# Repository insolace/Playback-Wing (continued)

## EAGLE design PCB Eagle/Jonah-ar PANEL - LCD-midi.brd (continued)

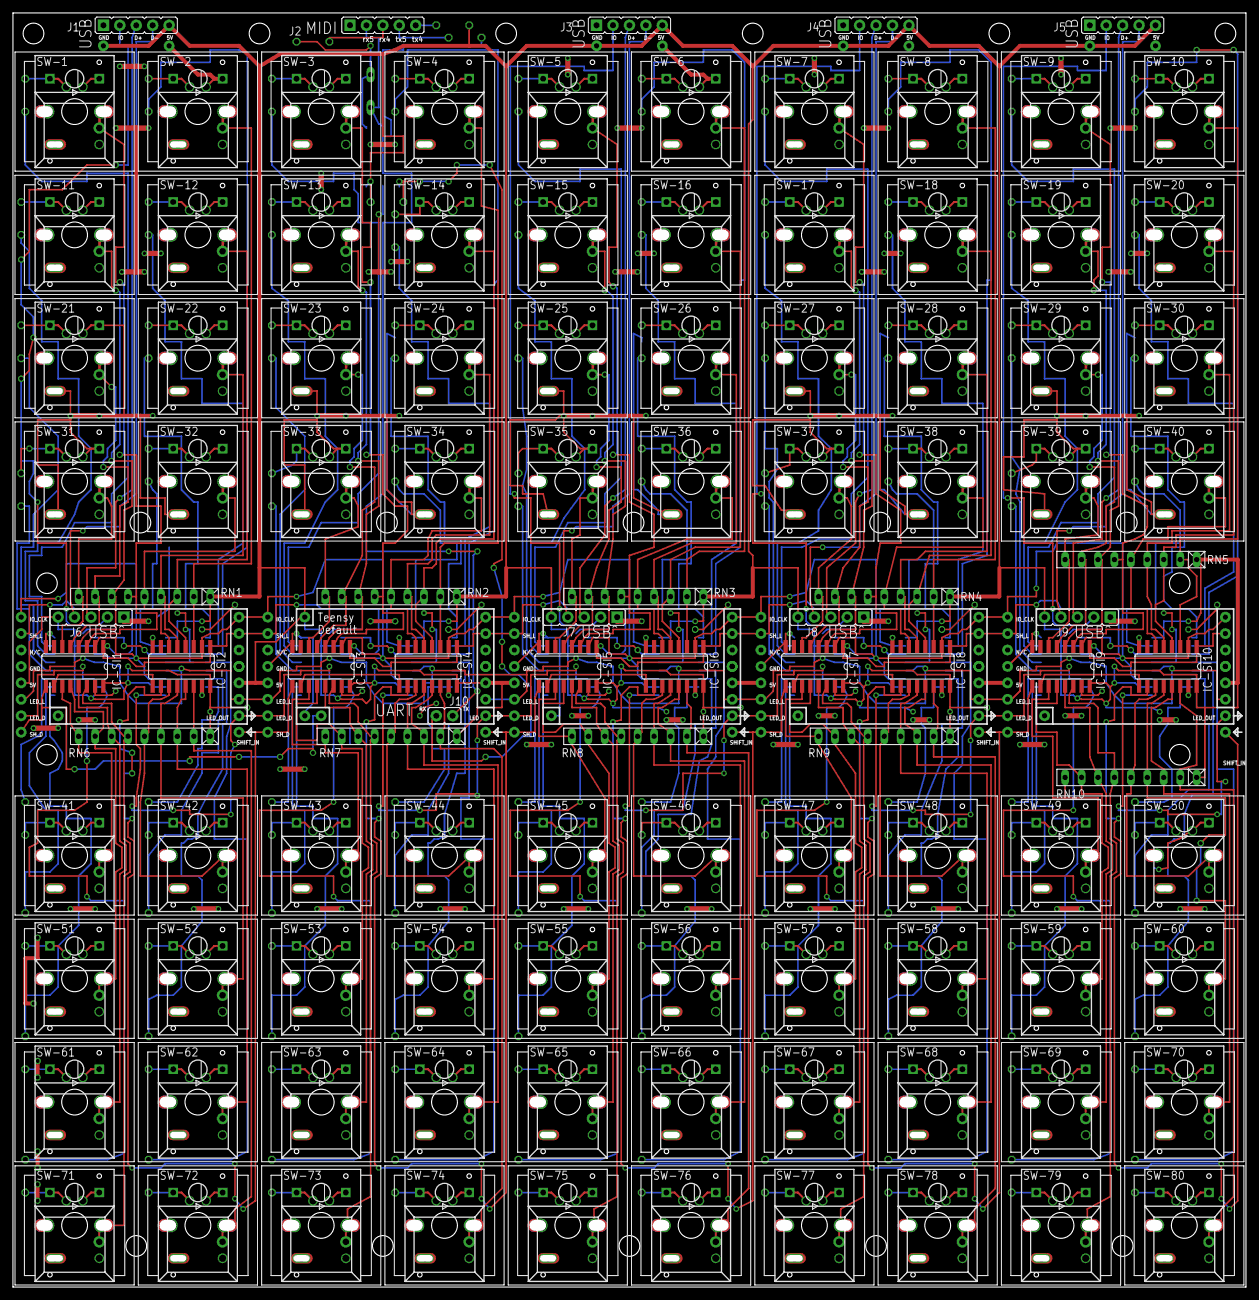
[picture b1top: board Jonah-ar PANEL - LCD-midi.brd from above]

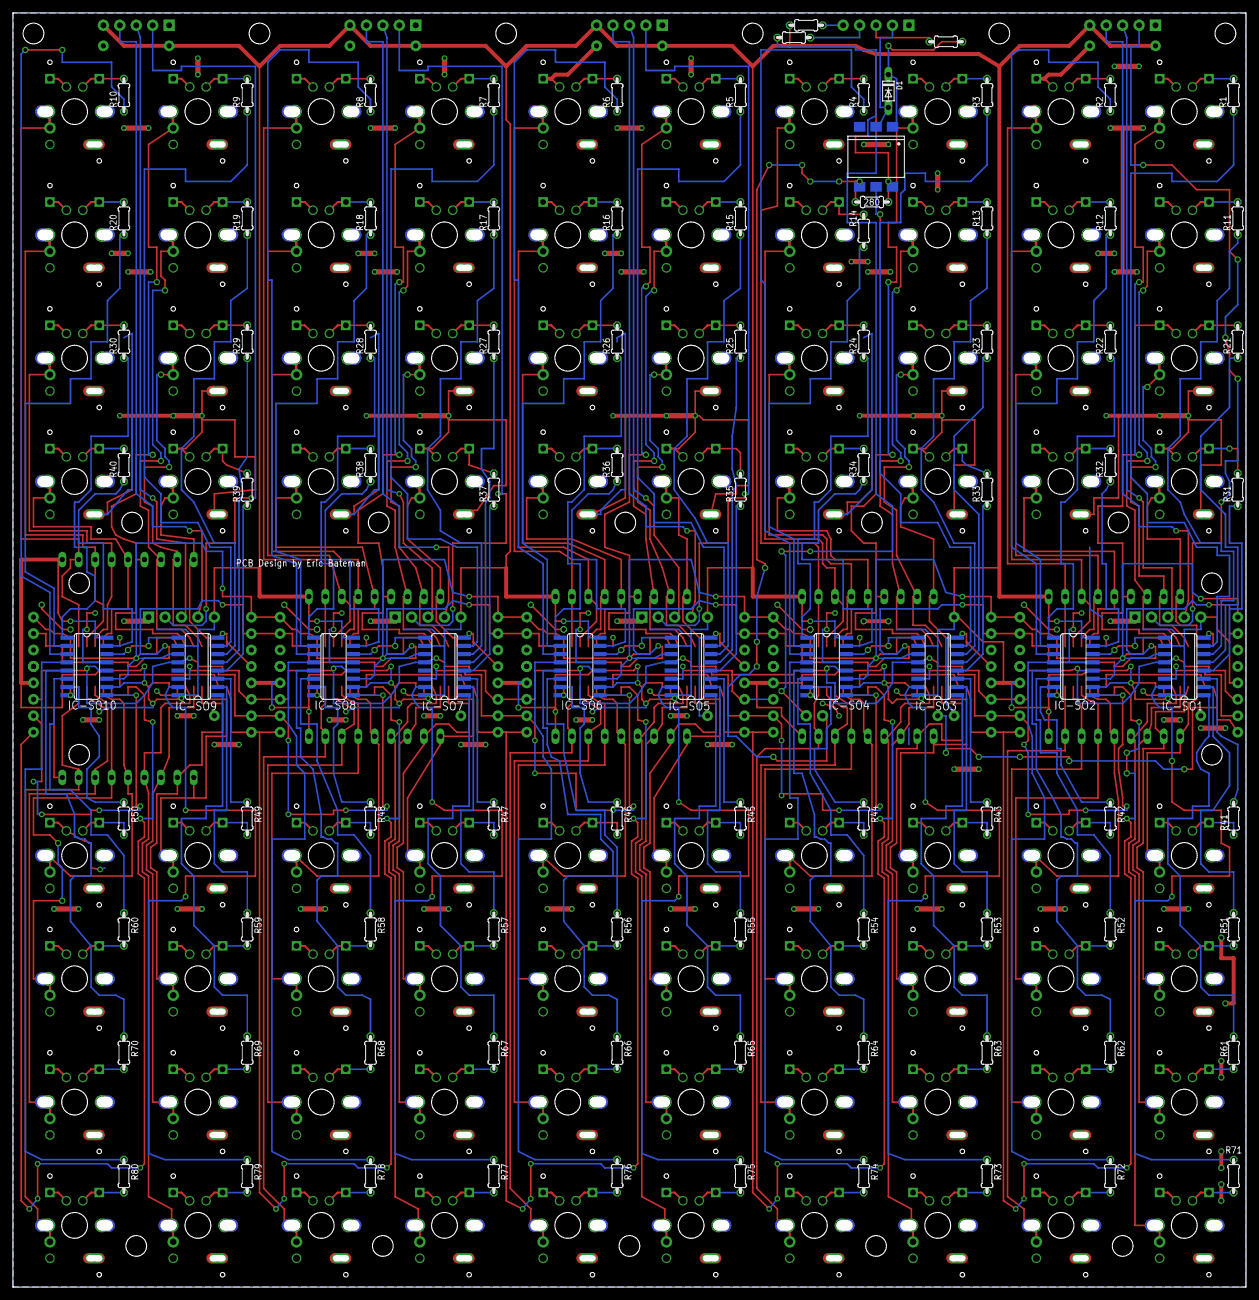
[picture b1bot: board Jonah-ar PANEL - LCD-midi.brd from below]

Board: 2 copper layers, 190.5 x 196.8 mm, 206 parts (96 on the bottom side), 282 nets.

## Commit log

2020-03-12 Add yt prevs
